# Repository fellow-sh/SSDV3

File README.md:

<p style="text-align: center;font-weight: bold;">This project has been migrated to the UBCO Aerospace Club <a href="https://github.com/UBCOAerospaceClub/2025_SSDV3">2025_SSDV3</a> fork.</p>

# The Super Step Down V3

The SSDV3 is an independently-made, non-isolated DC/DC converter designed for unmanned aerial systems (UAS). The module is intended for converting 50V battery input down to 5-12V output at a maximum load of 8A. It acts as a reliable battery-eliminator circuit (BEC) through effective regulation in the presence of voltage transients caused by high-power brushless motors.

## Specifications

<table><tbody>
  <tr>
    <td>Input Voltage</td>
    <td>20-60V</td>
  </tr>
  <tr>
    <td>Max Transient Voltage</td>
    <td>100V (clamping starts at 70V)</td>
  </tr>
  <tr>
    <td>Output Voltage(s)</td>
    <td>5.1V, 7.4V, 9.6V, 12V</td>
  </tr>
  <tr>
    <td>Thermal Max Output Current</td>
    <td>5A</td>
  </tr>
  <tr>
    <td>Designed Max Output Current</td>
    <td>8A</td>
  </tr>
  <tr>
    <td>Lowest Typical Efficiency</td>
    <td>89%</td>
  </tr>
  <tr>
    <td>Est. Voltage Overshoot</td>
    <td>200mV</td>
  </tr>
</tbody>
</table>

*Specifications are from design, not tested.*

## Comparison with Last Super Step Down

This design is motivated by the challenges encountered by the [UBCO Aerospace Club](https://github.com/UBCOAerospaceClub) with their Jellyfish quadcopter when powering auxiliary electronics off the drone's main battery. Lessons were learned through a variety of integration failures, investigations, and validation testing, and these experiences informed the development of version 3 of the Super Step Down series.

**Improvements from the previous version:**

- Dramatically improved regulation during line transients
- Considerable footprint area reduction by 16.5%
- Configurable output voltages instead of a fixed 5V output
- Added ESD protection on inputs
- Reverse polarity protection for the majority of the circuit
- Lower losses by using direct wire solder pads instead of terminal block

## Copyright Notice

Copyright &#169; Julian Joaquin 2025

Hardware Source Licensed under CERN-OHL-W version 2

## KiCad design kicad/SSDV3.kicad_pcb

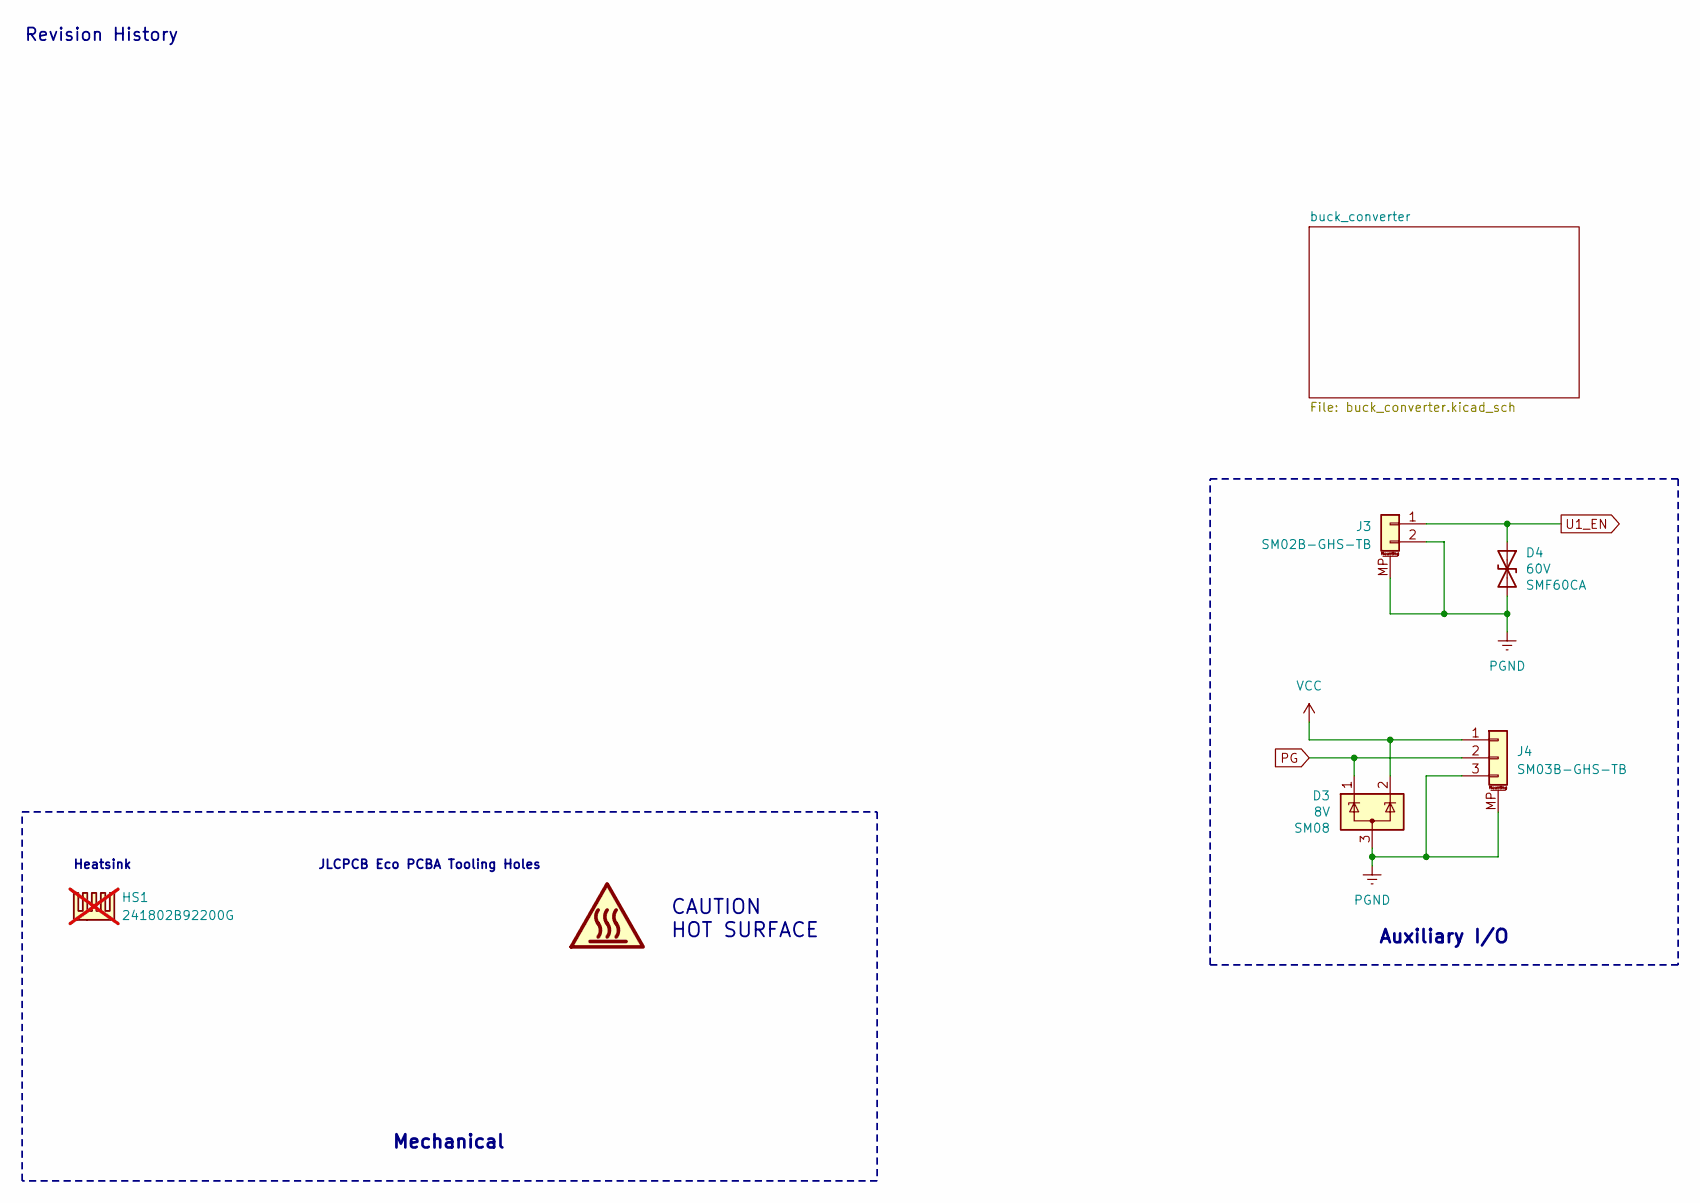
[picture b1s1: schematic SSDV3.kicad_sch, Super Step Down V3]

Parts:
D3: 8V; SOT-23-3; Voltage 8V; Part Number SM08; LCSC PN C42413902
D4: 60V; D_SMF; Voltage 60V; Part Number SMF60CA; LCSC PN C41376092
HS1: 241802B92200G; 24180xB9x200G; not fitted
J3: SM02B-GHS-TB; JST_GH_BM02B-GHS-TBT_1x02-1MP_P1.25mm_Vertical; Part Number SM02B-GHS-TB(LF)(SN); LCSC PN C189893
J4: SM03B-GHS-TB; JST_GH_BM03B-GHS-TBT_1x03-1MP_P1.25mm_Vertical; Part Number SM03B-GHS-TB(LF)(SN); LCSC PN C514175

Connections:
PG: D3.1 (K), J4.2; also elsewhere on the board
PGND: D3.3 (A), D4.2 (A2), J3.2, J3.MP (MountPin), J4.3, J4.MP (MountPin); also elsewhere on the board
U1_EN: D4.1 (A1), J3.1; also elsewhere on the board
VCC: D3.2 (K), J4.1; also elsewhere on the board

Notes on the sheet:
Heatsink
Auxiliary I/O
CAUTION HOT SURFACE
Revision History
JLCPCB Eco PCBA Tooling Holes
Mechanical

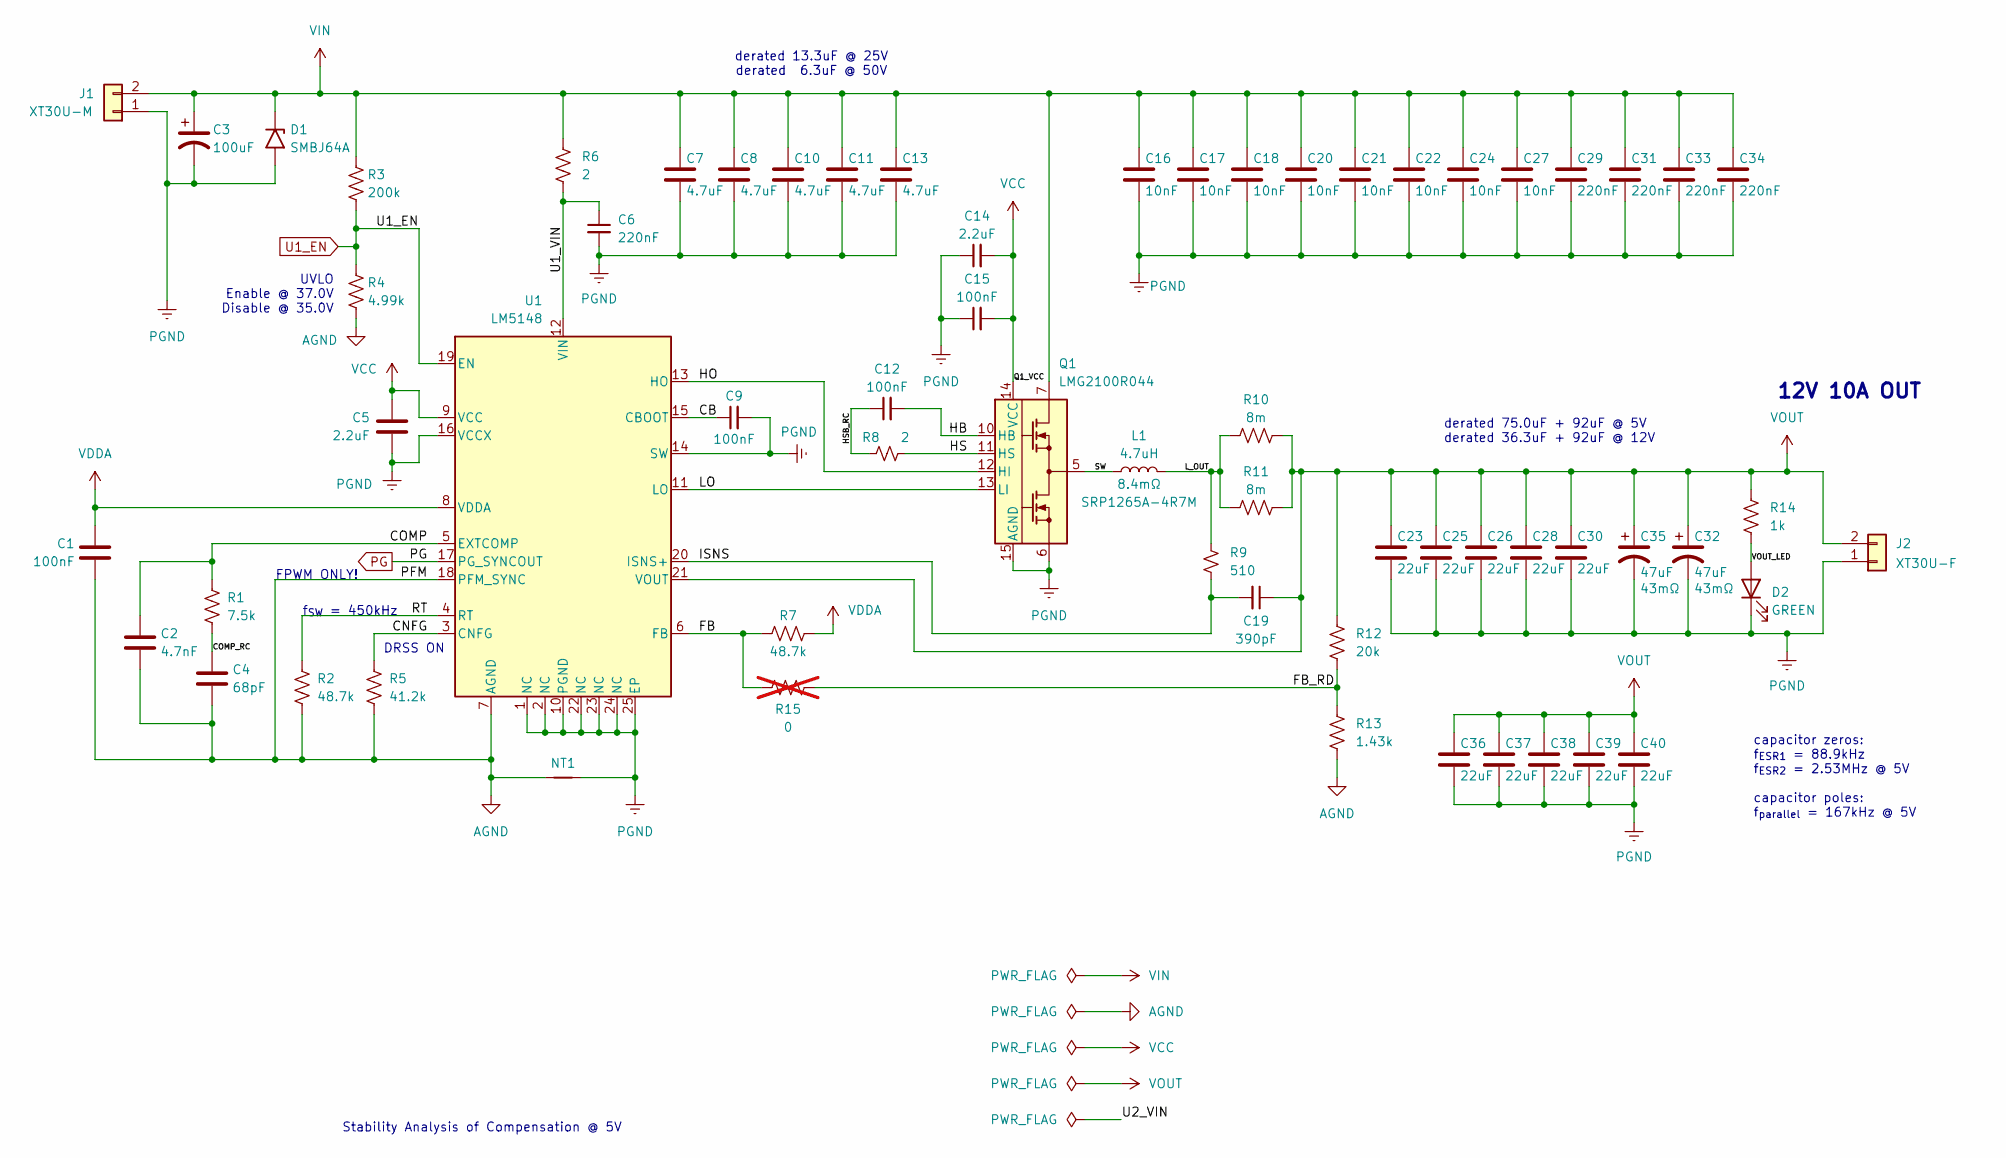
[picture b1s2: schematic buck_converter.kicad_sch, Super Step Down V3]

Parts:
C1, C12, C15: 100nF; C_0402_1005Metric; Voltage 100V; Tolerance 10%; Part Type Basic; LCSC PN C307331
C2: 4.7nF; C_0603_1608Metric_Pad1.08x0.95mm_HandSolder; Part Number CL10B472KB8NNNC; LCSC PN C1621
C3: 100uF; SolderWire-0.5sqmm_1x02_P4.6mm_D0.9mm_OD2.1mm
C4: 68pF; C_0603_1608Metric_Pad1.08x0.95mm_HandSolder; Part Number CL10C680JB8NNNC; LCSC PN C28262
C5, C14: 2.2uF; C_0603_1608Metric; Voltage 100V; Tolerance 10%; Part Type Extended; LCSC PN C415535
C6, C29, C31, C33, C34: 220nF; C_0603_1608Metric; Voltage 100V; Tolerance 10%; Part Type Extended; LCSC PN C7300906
C7, C8, C10, C11, C13: 4.7uF; C_1206_3216Metric_Pad1.33x1.80mm_HandSolder; Voltage 100V; Tolerance 10%; Part Type Extended; LCSC PN C3864744
C9: 100nF; C_0402_1005Metric; Part Number CL05B104KB54PNC; LCSC PN C307331
C16, C17, C18, C20, C21, C22, C24, C27: 10nF; C_0402_1005Metric; Voltage 100V; Tolerance 10%; Part Type Extended; LCSC PN C527014
C19: 390pF; C_0402_1005Metric; Voltage 100V; Tolerance 10%; Part Type Extended; LCSC PN C2168577
C23, C25, C26, C28, C30, C36, C37, C38, C39, C40: 22uF; C_0805_2012Metric; Voltage 25V; Tolerance 20%; Part Type Extended; LCSC PN C86816
C32, C35: 47uF; CAP_TQC_B2_PAN; Tolerance 20%; Voltage 16V; Part Type Extended; LCSC PN C4987277
D1: SMBJ64A; D_SMB; Part Number SMBJ64A; LCSC PN C19077594
D2: GREEN; LED_0805_2012Metric; Part Type Basic; LCSC PN C2297
J1: XT30U-M; AMASS_XT30U-M_1x02_P5.0mm_Vertical; Part Number XT30U-M; LCSC PN C99101
J2: XT30U-F; AMASS_XT30U-F_1x02_P5.0mm_Vertical; Part Number XT30U-F; LCSC PN C99102
L1: 4.7uH; L_Bourns_SRP1245A; Tolerance 20%; Part Number SRP1265A-4R7M; LCSC PN C780205
NT1: NetTie_2; NetTie-2_SMD_Pad0.5mm
Q1: LMG2100R044; RAR0016B-MFG; Part Number LMG2100R044RARR; LCSC PN C22453052
R1: 7.5k; R_0603_1608Metric_Pad0.98x0.95mm_HandSolder; Part Number 0603WAF7501T5E; LCSC PN C23234
R2, R7: 48.7k; R_0603_1608Metric; Part Number RC0603FR-0748K7L; LCSC PN C165749
R3: 200k; R_0402_1005Metric; Part Number 0402WGF2003TCE; LCSC PN C25764
R4: 4.99k; R_0603_1608Metric_Pad0.98x0.95mm_HandSolder; Part Number 0603WAF4991T5E; LCSC PN C23046
R5: 41.2k; R_0402_1005Metric; Part Number RC0402FR-0741K2L; LCSC PN C185416
R6: 2; R_0402_1005Metric_Pad0.72x0.64mm_HandSolder; Voltage 75V; Tolerance 1%; Part Type Extended; LCSC PN C270630
R8: 2; R_0402_1005Metric_Pad0.72x0.64mm_HandSolder; Part Number 0402WGF200KTCE; LCSC PN C270630
R9: 510; R_0402_1005Metric; Part Number 0402WGF5100TCE; LCSC PN C25123
R10, R11: 8m; R_1206_3216Metric; Part Number PE1206FRM470R008L; LCSC PN C1720323
R12: 20k; R_0603_1608Metric_Pad0.98x0.95mm_HandSolder; Part Number 0603WAF2002T5E; LCSC PN C4184
R13: 1.43k; R_0603_1608Metric_Pad0.98x0.95mm_HandSolder; Part Number RT0603BRE071K43L; LCSC PN C861730
R14: 1k; R_0805_2012Metric; Voltage 150V; Tolerance 1%; Part Type Basic; LCSC PN C17513
R15: 0; R_0603_1608Metric_Pad0.98x0.95mm_HandSolder; Part Number RC0603JR-070RL; LCSC PN C95177; not fitted
U1: LM5148; Texas_RGY0024F_EP_3.5x5.5mm_P0.5_ThermalVias-D0.2mm; Part Number LM5148RGYR; LCSC PN C7470701

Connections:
/buck_converter/CB: C9.1, U1.15 (CBOOT)
/buck_converter/CNFG: R5.1, U1.3 (CNFG)
/buck_converter/COMP: C2.1, R1.1, U1.5 (EXTCOMP)
/buck_converter/COMP_RC: C4.1, R1.2
/buck_converter/FB: R7.1, R15.1, U1.6 (FB)
/buck_converter/FB_RD: R12.2, R13.1, R15.2
/buck_converter/HB: C12.2, Q1.10 (HB)
/buck_converter/HO: Q1.12 (HI), U1.13 (HO)
/buck_converter/HS: Q1.11 (HS), R8.2
/buck_converter/HSB_RC: C12.1, R8.1
/buck_converter/ISNS: C19.2, R9.2, U1.20 (ISNS+)
/buck_converter/LO: Q1.13 (LI), U1.11 (LO)
/buck_converter/L_OUT: L1.2, R9.1, R10.1, R11.1
/buck_converter/RT: R2.1, U1.4 (RT)
/buck_converter/SW: L1.1, Q1.5
/buck_converter/U1_VIN: C6.1, R6.2, U1.12 (VIN)
/buck_converter/VOUT_LED: D2.2 (A), R14.2
AGND: C1.2, C2.2, C4.2, NT1.1, R2.2, R4.2, R5.2, R13.2, U1.7 (AGND), U1.18 (PFM_SYNC)
PG: U1.17 (PG_SYNCOUT); also elsewhere on the board
PGND: C3.2, C5.2, C6.2, C7.2, C8.2, C9.2, C10.2, C11.2, C13.2, C14.1, C15.1, C16.2, C17.2, C18.2, C20.2, C21.2, C22.2, C23.2, C24.2, C25.2, C26.2, C27.2, C28.2, C29.2, C30.2, C31.2, C32.2, C33.2, C34.2, C35.2, C36.2, C37.2, C38.2, C39.2, C40.2, D1.2 (A2), D2.1 (K), J1.1, J2.1, NT1.2, Q1.6, Q1.15 (AGND), Q1.17, U1.1 (NC), U1.2 (NC), U1.10 (PGND), U1.14 (SW), U1.16 (VCCX), U1.22 (NC), U1.23 (NC), U1.24 (NC), U1.25 (EP); also elsewhere on the board
U1_EN: R3.2, R4.1, U1.19 (EN); also elsewhere on the board
VCC: C5.1, C14.2, C15.2, Q1.14 (VCC), U1.9 (VCC); also elsewhere on the board
VDDA: C1.1, R7.2, U1.8 (VDDA)
VIN: C3.1, C7.1, C8.1, C10.1, C11.1, C13.1, C16.1, C17.1, C18.1, C20.1, C21.1, C22.1, C24.1, C27.1, C29.1, C31.1, C33.1, C34.1, D1.1 (A1), J1.2, Q1.7, R3.1, R6.1
VOUT: C19.1, C23.1, C25.1, C26.1, C28.1, C30.1, C32.1, C35.1, C36.1, C37.1, C38.1, C39.1, C40.1, J2.2, R10.2, R11.2, R12.1, R14.1, U1.21 (VOUT)

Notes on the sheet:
capacitor zeros: f_{ESR1} = 88.9kHz f_{ESR2} = 2.53MHz @ 5V capacitor poles: f_{parallel} = 167kHz @ 5V
FPWM ONLY!
Stability Analysis of Compensation @ 5V
DRSS ON
12V 10A OUT
derated 13.3uF @ 25V derated 6.3uF @ 50V
UVLO Enable @ 37.0V Disable @ 35.0V
derated 75.0uF + 92uF @ 5V derated 36.3uF + 92uF @ 12V
f_{SW} = 450kHz

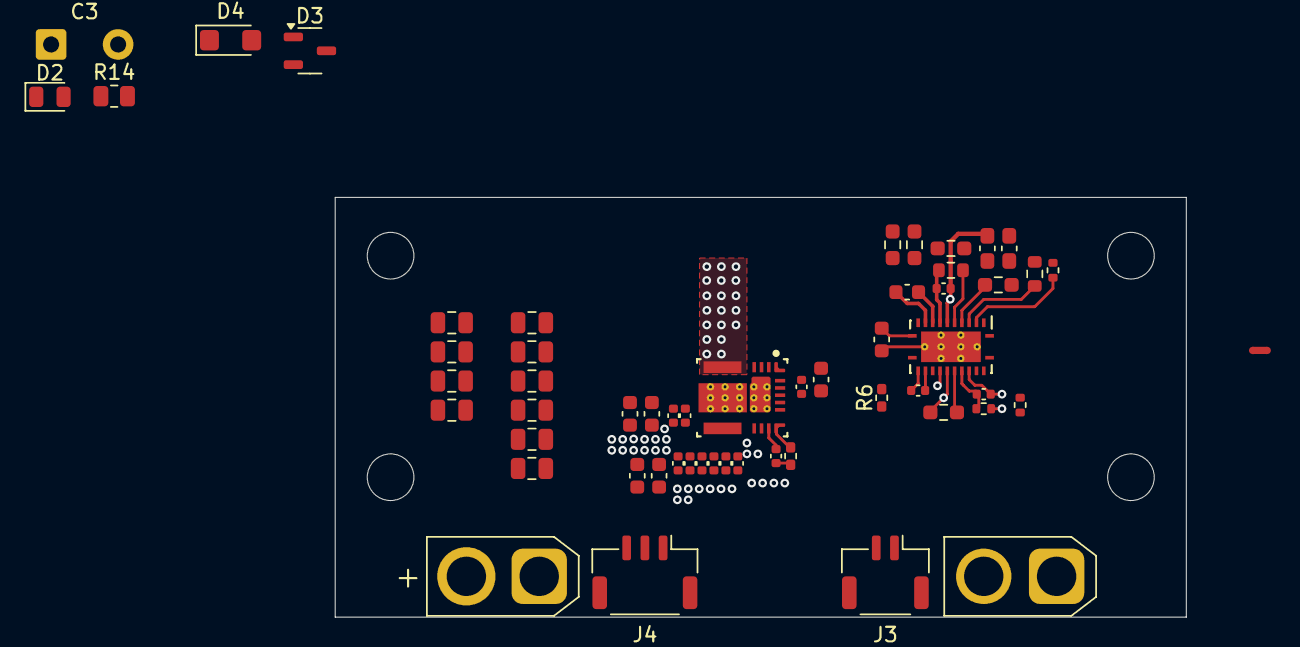
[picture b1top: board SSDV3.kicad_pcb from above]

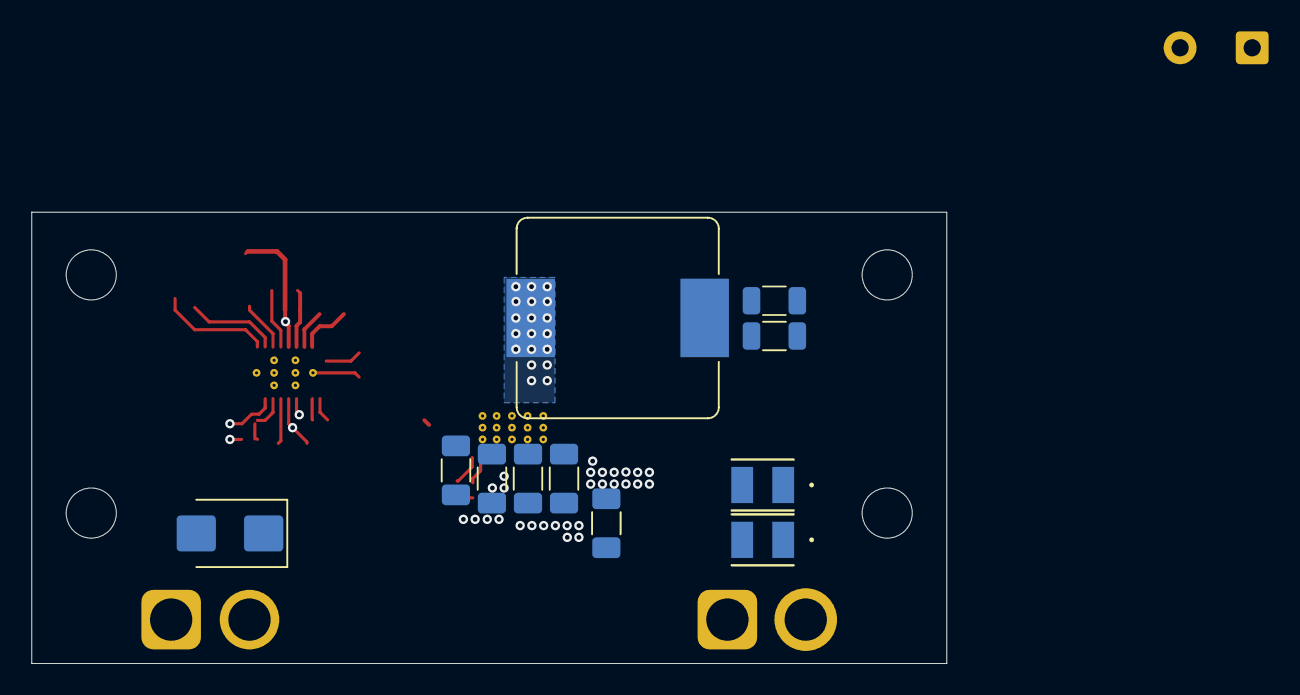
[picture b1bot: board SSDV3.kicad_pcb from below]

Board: 4 copper layers, 58.4 x 28.8 mm, 68 parts (11 on the bottom side), 25 nets.

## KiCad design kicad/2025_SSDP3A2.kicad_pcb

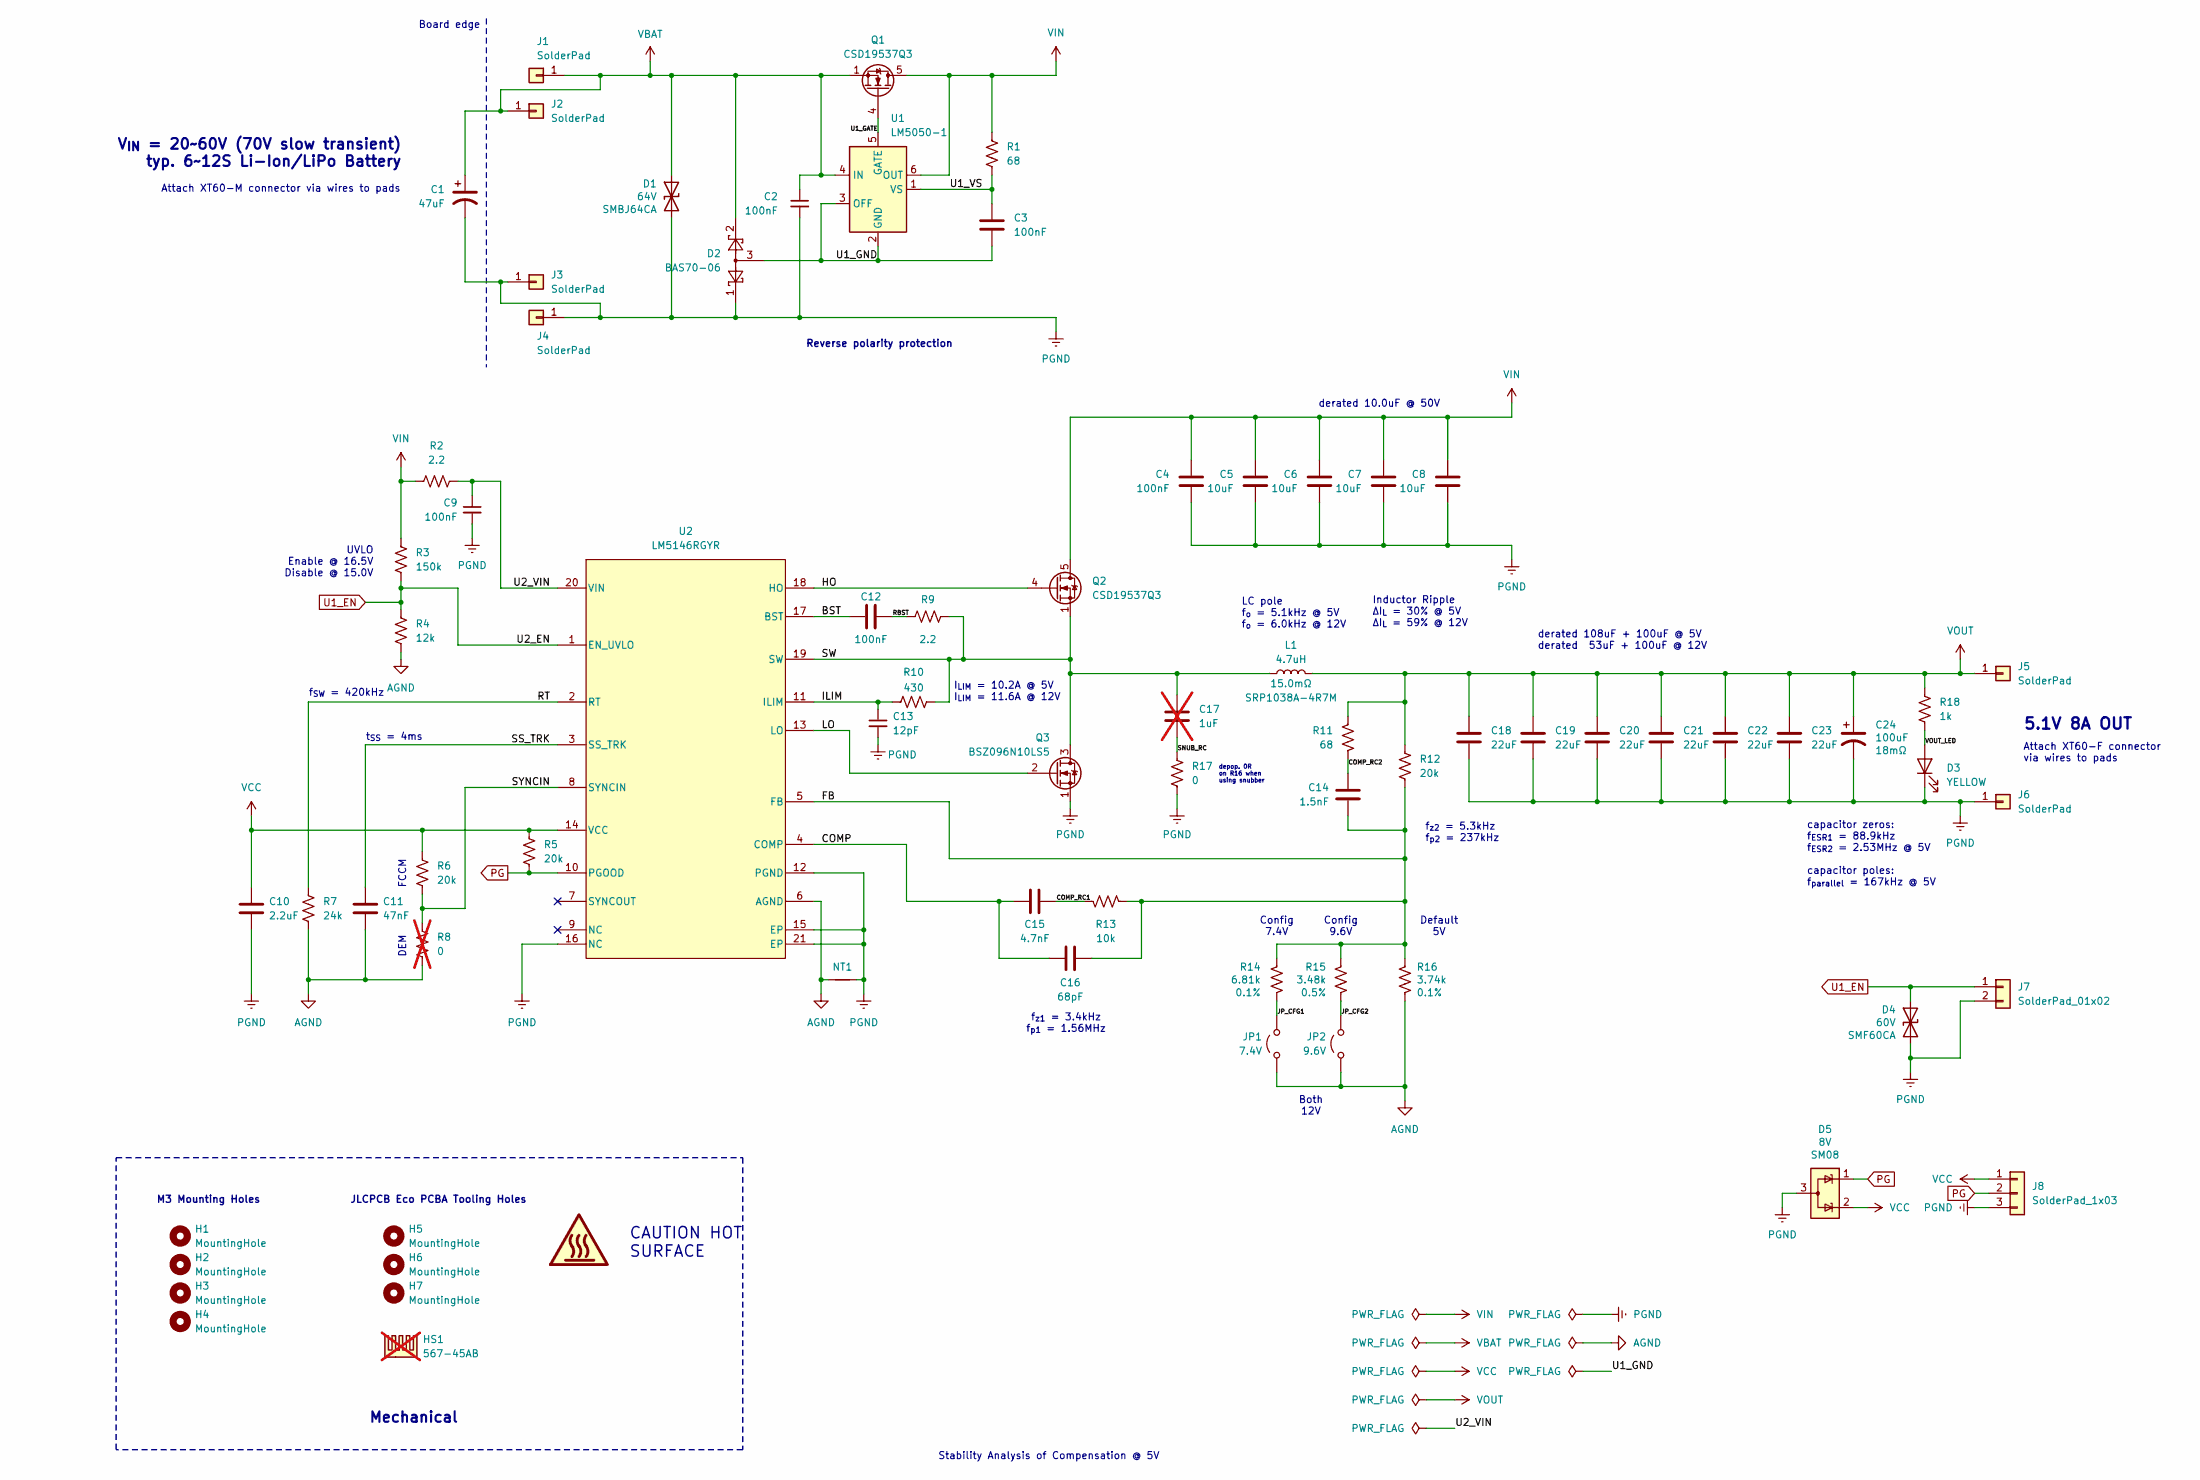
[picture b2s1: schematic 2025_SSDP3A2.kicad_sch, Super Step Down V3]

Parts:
C1: 47uF; Part Number ESH476M100AH9AA; LCSC PN C5113349
C2, C3, C4, C9, C12: 100nF; C_0603_1608Metric; Voltage 100V; Tolerance 10%; Part Type Extended; LCSC PN C113803
C5, C6, C7, C8: 10uF; C_1210_3225Metric; Voltage 100V; Tolerance 10%; Part Type Extended; LCSC PN C576517
C10: 2.2uF; C_0805_2012Metric; Voltage 50V; Tolerance 10%; Part Type Basic; LCSC PN C377773
C11: 47nF; C_0603_1608Metric; Voltage 50V; Tolerance 10%; Part Type Basic; LCSC PN C1622
C13: 12pF; C_0603_1608Metric; Voltage 100V; Tolerance 5%; Part Type Extended; LCSC PN C576801
C14: 1.5nF; C_0603_1608Metric; Voltage 50V; Tolerance 10%; Part Type Preferred Extended; LCSC PN C1595
C15: 4.7nF; C_0603_1608Metric; Voltage 50V; Tolerance 10%; Part Type Basic; LCSC PN C53987
C16: 68pF; C_0603_1608Metric; Voltage 50V; Tolerance 5%; Part Type Preferred Extended; LCSC PN C28262
C17: 1uF; C_0603_1608Metric_Pad1.08x0.95mm_HandSolder; not fitted
C18, C19, C20, C21, C22, C23: 22uF; C_1210_3225Metric; Voltage 25V; Tolerance 10%; Part Type Extended; LCSC PN C52306
C24: 100uF; CP_EIA-7343-20_Kemet-V_HandSolder; Tolerance 20%; Voltage 25V; Part Type Extended; LCSC PN C696814
D1: 64V; D_SMB; Voltage 103V; Part Number SMBJ64CA; LCSC PN C41376099
D2: BAS70-06; SOT-23-3; Part Number BAS70-06; LCSC PN C22466364
D3: YELLOW; LED_0805_2012Metric; Part Type Basic; LCSC PN C2296
D4: 60V; D_SMF; Voltage 60V; Part Number SMF60CA; LCSC PN C41376092
D5: 8V; SOT-23-3; Voltage 8V; Part Number SM08; LCSC PN C42413902
H1, H2, H3, H4: MountingHole; MountingHole_3.2mm_M3_ISO7380
H5, H6, H7: MountingHole; ToolingHole_1.152mm
HS1: 567-45AB; not fitted
J1, J4, J5, J6: SolderPad; SolderWirePad_1x01_SMD_3x6mm
J2, J3: SolderPad; SolderWirePad_1x01_SMD_1.5x3mm
J7: SolderPad_01x02; SolderWirePad_1x02_SMD_1.5x2mm
J8: SolderPad_1x03; SolderWirePad_1x03_SMD_1.5x2mm
JP1: 7.4V; SolderJumper-2_P1.3mm_Open_TrianglePad1.0x1.5mm
JP2: 9.6V; SolderJumper-2_P1.3mm_Open_TrianglePad1.0x1.5mm
L1: 4.7uH; L_Bourns_SRP1038C_10.0x10.0mm; Tolerance 20%; Part Number SRP1038A-4R7M; LCSC PN C2041319
NT1: NetTie_2; NetTie-2_SMD_Pad0.5mm
Q1: CSD19537Q3; Texas_DQG0008A_3.3x3.3mm_P0.65mm_ThermalVias-D0.3mm; Part Number CSD19537Q3T; LCSC PN C134143
Q2: CSD19537Q3; Texas_DQG0008A_3.3x3.3mm_P0.65mm_ThermalVias-D0.3mm; Voltage 100V; Part Type Extended; LCSC PN C134143
Q3: BSZ096N10LS5; Infineon_PG-TSDSON-8-26_3.3x3.3mm_P0.65mm; Voltage 100V; Part Number BSZ096N10LS5; LCSC PN C534695
R1, R11: 68; R_0603_1608Metric; Voltage 75V; Tolerance 1%; Part Type Preferred Extended; LCSC PN C27592
R2, R9: 2.2; R_0603_1608Metric; Voltage 75V; Tolerance 1%; Part Type Basic; LCSC PN C22939
R3: 150k; R_0603_1608Metric; Tolerance 1%; Voltage 75V; Part Type Basic; LCSC PN C22807
R4: 12k; R_0603_1608Metric; Tolerance 1%; Voltage 75V; Part Type Basic; LCSC PN C22790
R5, R6, R12: 20k; R_0603_1608Metric; Voltage 75V; Tolerance 1%; Part Type Basic; LCSC PN C4184
R7: 24k; R_0603_1608Metric; Voltage 75V; Tolerance 1%; Part Type Basic; LCSC PN C23352
R8: 0; R_0603_1608Metric; not fitted
R10: 430; R_0603_1608Metric; Voltage 75V; Tolerance 1%; Part Type Preferred Extended; LCSC PN C23170
R13: 10k; R_0603_1608Metric; Voltage 75V; Tolerance 1%; Part Type Basic; LCSC PN C25804
R14: 6.81k; R_0603_1608Metric; Voltage 50V; Tolerance 0.1%; Part Type Extended; LCSC PN C861538
R15: 3.48k; R_0603_1608Metric; Voltage 50V; Tolerance 0.5%; Part Type Extended; LCSC PN C423043
R16: 3.74k; R_0603_1608Metric; Tolerance 0.1%; Voltage 75V; Part Type Extended; LCSC PN C849741
R17: 0; R_1206_3216Metric_Pad1.30x1.75mm_HandSolder; Tolerance 1%; Voltage 200V; Part Type Basic; LCSC PN C17888
R18: 1k; R_0805_2012Metric; Voltage 150V; Tolerance 1%; Part Type Basic; LCSC PN C17513
U1: LM5050-1; TSOT-23-6; Part Number LM5050-1; LCSC PN C473393
U2: LM5146RGYR; RGY0020B-MFG; Voltage 100V; Part Type Extended; LCSC PN C3188679

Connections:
/BST: C12.2, U2.17 (BST)
/COMP: C15.1, C16.2, U2.4 (COMP)
/COMP_RC1: C15.2, R13.2
/COMP_RC2: C14.1, R11.2
/FB: C14.2, C16.1, R12.2, R13.1, R14.1, R15.1, R16.1, U2.5 (FB)
/HO: Q2.4 (G), U2.18 (HO)
/ILIM: C13.1, R10.2, U2.11 (ILIM)
/JP_CFG1: JP1.2 (B), R14.2
/JP_CFG2: JP2.2 (B), R15.2
/LO: Q3.2 (G), U2.13 (LO)
/RBST: C12.1, R9.1
/RT: R7.1, U2.2 (RT)
/SNUB_RC: C17.2, R17.1
/SS_TRK: C11.1, U2.3 (SS_TRK)
/SW: C17.1, L1.1, Q2.1 (S), Q2.2 (S), Q2.3 (S), Q3.3 (D), R9.2, R10.1, U2.19 (SW)
/SYNCIN: R6.2, R8.1, U2.8 (SYNCIN)
/U1_GATE: Q1.4 (G), U1.5 (GATE)
/U1_GND: C3.2, D2.3, U1.2 (GND), U1.3 (OFF)
/U1_VS: C3.1, R1.2, U1.1 (VS)
/U2_VIN: C9.1, R2.2, U2.20 (VIN)
/VOUT_LED: D3.2 (A), R18.2
AGND: C11.2, JP1.1 (A), JP2.1 (A), NT1.1, R4.2, R7.2, R8.2, R16.2, U2.6 (AGND)
PG: D5.1 (K), J8.2, R5.2, U2.10 (PGOOD)
PGND: C1.2, C2.2, C4.2, C5.2, C6.2, C7.2, C8.2, C9.2, C10.2, C13.2, C18.2, C19.2, C20.2, C21.2, C22.2, C23.2, C24.2, D1.2 (A2), D2.1, D3.1 (K), D4.2 (A2), D5.3 (A), J3.1, J4.1, J6.1, J7.2, J8.3, NT1.2, Q3.1 (S), R17.2, U2.12 (PGND), U2.15 (EP), U2.16 (NC), U2.21 (EP)
U1_EN: D4.1 (A1), J7.1, R3.2, R4.1, U2.1 (EN_UVLO)
VBAT: C1.1, C2.1, D1.1 (A1), D2.2, J1.1, J2.1, Q1.1 (S), Q1.2 (S), Q1.3 (S), U1.4 (IN)
VCC: C10.1, D5.2 (K), J8.1, R5.1, R6.1, U2.14 (VCC)
VIN: C4.1, C5.1, C6.1, C7.1, C8.1, Q1.5 (D), Q2.5 (D), R1.1, R2.1, R3.1, U1.6 (OUT)
VOUT: C18.1, C19.1, C20.1, C21.1, C22.1, C23.1, C24.1, J5.1, L1.2, R11.1, R12.1, R18.1

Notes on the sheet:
DEM
V_{IN} = 20~60V (70V slow transient) typ. 6~12S Li-Ion/LiPo Battery
Attach XT60-F connector via wires to pads
Default 5V
Reverse polarity protection
M3 Mounting Holes
I_{LIM} = 10.2A @ 5V I_{LIM} = 11.6A @ 12V
Attach XT60-M connector via wires to pads
capacitor zeros: f_{ESR1} = 88.9kHz f_{ESR2} = 2.53MHz @ 5V capacitor poles: f_{parallel} = 167kHz @ 5V
Both 12V
Inductor Ripple ΔI_{L} = 30% @ 5V ΔI_{L} = 59% @ 12V
CAUTION HOT SURFACE
depop. 0R on R16 when using snubber
derated 10.0uF @ 50V
f_{SW} = 420kHz
Board edge
FCCM
f_{z1} = 3.4kHz f_{p1} = 1.56MHz
LC pole f_{o} = 5.1kHz @ 5V f_{o} = 6.0kHz @ 12V
UVLO Enable @ 16.5V Disable @ 15.0V
5.1V 8A OUT
Config 7.4V
Config 9.6V
JLCPCB Eco PCBA Tooling Holes
f_{z2} = 5.3kHz f_{p2} = 237kHz
Stability Analysis of Compensation @ 5V
derated 108uF + 100uF @ 5V derated 53uF + 100uF @ 12V
t_{SS} = 4ms
Mechanical

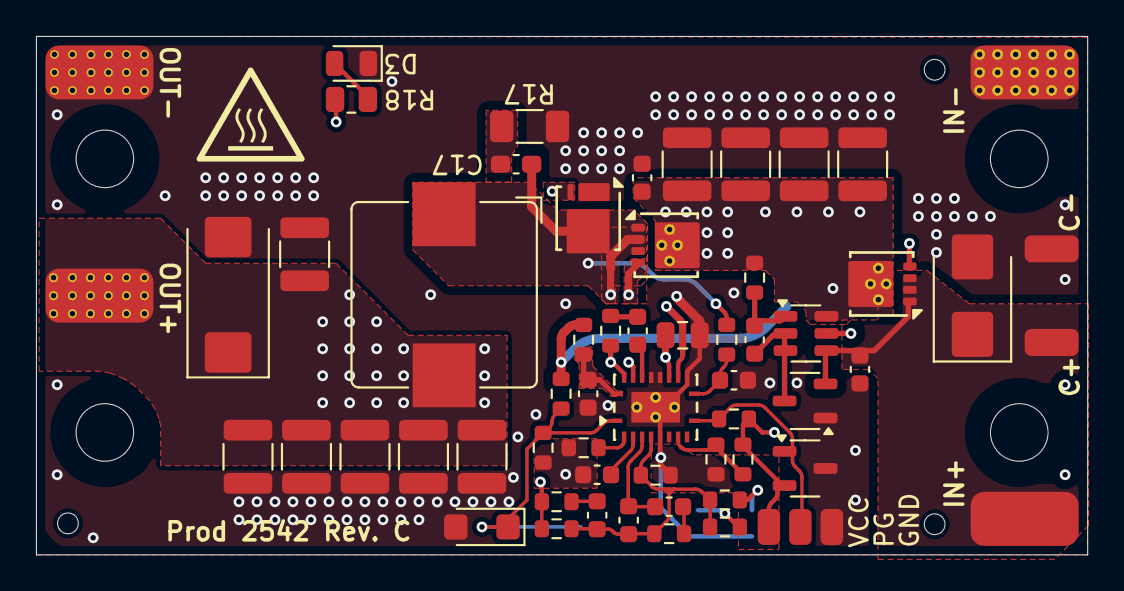
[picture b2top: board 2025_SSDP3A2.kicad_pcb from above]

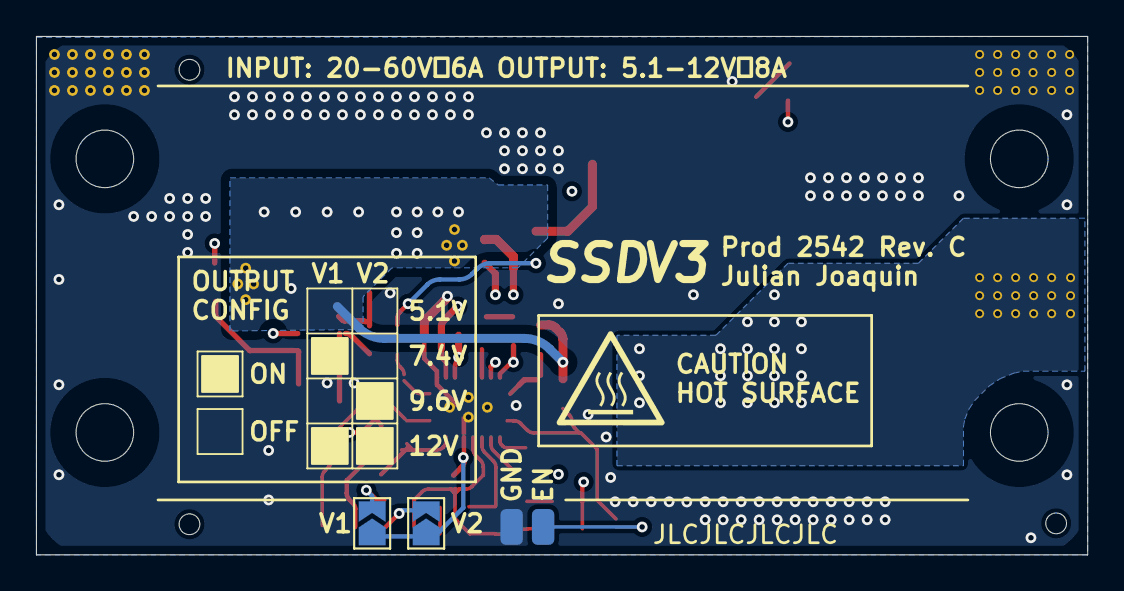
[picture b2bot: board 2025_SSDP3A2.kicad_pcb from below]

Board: 4 copper layers, 58.4 x 28.8 mm, 70 parts (3 on the bottom side), 29 nets.

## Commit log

2025-09-19 Updated pdf
2025-09-20 Revised PCB layout
2025-09-20 Note to change iLim
2025-09-21 Revised MOSFET selection
2025-09-22 Revised ILIM setting, added TVS
2025-09-22 Revised PCB layout, simplified EMI filter
2025-09-22 Validated soft start circuit
2025-09-23 Updated ILIM values
2025-09-24 Something changed
2025-09-25 Added soft-start concept
2025-09-25 Updated schematic
2025-09-26 Revised simulations, revised compensation network
2025-09-29 Changed output capacitors for better layout
2025-09-29 Corrected date
2025-09-29 Began board routing, added README
2025-09-29 Corrected hot-swap simulation
2025-09-29 Revised output cap placement
2025-09-30 Removed soldermask around screw holes
2025-09-30 Revised mounting holes, bode plot, routing
2025-09-30 Adjusted revision system
2025-10-01 Using PQFN FETs instead of SuperSO-8
2025-10-01 Finished routing
2025-10-01 Added silkscreen markings, tweaked routing
2025-10-01 Tweaked routing, changed some fab parameters
2025-10-03 Tweaked routing
2025-10-04 Tweaked feedback routing
2025-10-04 Tweaked feedback routing and removed EMI filter
    The EMI filter places an inductor in between the battery and the buck
    converter, creating the risk of resonance either at the buck converter
    input or on the battery line. While the former issue has been *somewhat*
    addressed with the parallel damping resistor, the latter issue cannot be
    reasonably fixed without good knowledge of the other various loads that
    may be attached to the battery line. For this reason, the EMI filter is
2025-10-04 Changed schematic and board pictures
2025-10-04 Tweaked routing layers
2025-10-05 Tweaked routing, added breakout pads, via clean up
2025-10-05 Added 7.4V output support
2025-10-05 Final tweaks
2025-10-06 Added more capacitors to meet overshoot requirements
2025-10-06 Tweaks in schematic and layout
2025-10-06 Changed TVS diode
2025-10-08 Revised input TVS and added input cap
2025-10-10 Slightly bigger vout area
2025-10-11 Improvements to copper, added schematic notations
2025-10-11 Improvements to copper, EMI reduction techniques
2025-10-11 Updated schematic, added more silkscreen markings
2025-10-12 Added more thermal area
2025-10-13 Added TVS protection to aux IO
2025-10-14 Verified compensation network
2025-10-16 Changed parts for LCSC availability, added silkscreen markings
2025-10-16 Fixed manufacturing errors
2025-10-16 Changed part parameterization
2025-10-16 RevC has input polarity protection
2025-10-16 Fixed description typo
2025-10-17 Fixed BOM typo
2025-10-17 Fixed value typo
2025-10-17 Added missing thermal vias
2025-10-17 Repository cleanup
2025-10-19 Removed unnecessary files
2025-10-20 Removed license-restricted files
2025-10-20 Officially now the SSDV3
2025-10-20 Fixed paste overlapping soldermask
2025-10-22 Minor layout improvements, using original footprints
2025-10-24 Minor layout improvements, improved TSDSON-8 S-D clearance
2025-10-24 Improved LM5146 footprint
2025-10-31 Added schematic details, added license, improved README
2025-10-31 Updated project documents files
2025-11-03 revD started, fixed reverse polarity issues and improve temp rating
2025-11-05 Refactored schematic into A4 paper, updated PDFs
2025-11-09 Layout tweaks, added copyright notice
2026-02-05 Initial layout for version 4

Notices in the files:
kicad/SSDV3.kicad_sch:
Copyright © Julian Joaquin, 2026
